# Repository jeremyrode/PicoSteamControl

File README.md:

# PicoSteamControl
This project implements a new Raspberry Pi Pico based control for a [Leisure Steam One Touch LS series steam generator](https://leisure-steam.com/product-category/steam-generators/1-touch-steam-unit/).

The factory control PCB was misbehaving, and I have wanted to implement an automatic self-flush to clean the tank, so I thought it would be a good challenge to replace it with a Raspberry Pi Pico.

This is my first MicroPython project.  I was originally implementing this system in C, but when I started down the path to connect a Pico W to WiFi, I decided to try out MicroPython and I was blown away by the power and rapid development/test cycles.

I mostly think this project might be interesting to people because of a few new ideas that I have not seen documented well in the wild:

# New ideas:

This project served as a testbed for 3 new ideas that I wanted to try:
- Status Logging and Timestamping though WiFi
- Capacitive Touch Sensing via a PIO State Machine
- New Ideal Diode Peak Detector CT Interface

## Status Logging and Timestamping though WiFi

A major reason I was implementing much of my IoT work with boards that run full Linux (usually a Raspberry Pi Zero W) is logging and timestamping functionality.  Many of these IoT systems are very difficult to debug without a persistent log that is timestamped.  Both storing and retrieving persistent logs (to some sort of nonvolatile memory) and getting real time (UTC) on a microcontroller are difficult.

Here, this is solved by sending my log messages out to Raspberry Pi with NTP running via the network and urequests libraries:

```python
def logWifi(logmessage):
    print('Log: ' + logmessage)
    res = requests.post(secrets.url, data = logmessage)
```

Remarkably simple and effective, this server could easily serve many Pico W boards. See main.py for the full code with WiFi reconnection, and error handling.  [The secrets.url uses a config file to not check in WiFi passwords or local IPs to a public Git.]( https://www.coderdojotc.org/micropython/wireless/02-connecting-to-wifi/ "MicroPython WiFi Info")

The logWifi() function in main.py takes the log request and sends it to a http server (SteamLogger.js) running in Node.js that timestamps it and writes it to a file.

```node
const server = http.createServer((req, res) => {
  if (req.method === 'POST') {
    let data = '';
    req.on('data', chunk => {
      data += chunk.toString();
    });
    req.on('end', () => {
      let curDate = new Date();
      let dateStr = curDate.toString();
      message = dateStr.slice(0,dateStr.length-33) + ' ' + data; //Prepend Time to message
      console.log(message);
      logfile.write(message + '\n')
      res.end('OK');
    });
  }
});
```
Note that this code was upgraded into batch mode via Gemini.

## Capacitive Touch Sensing via PIO State Machine

After discovering that the control button on the LS1 one touch is a capacitive membrane switch, I investigated specific ICs that detect capacitive touch sensing, but this is a perfect task for a PIO state machine. This PIO-based detection ended up very reliable and has very good dynamic range: Around 250K cycles for the untouched state, and with a strong push increasing this to 6-8M cycles.  A logging function serves to quantify the reliability. 

Here is a very unoptimized PIO state machine that charges a capacitive touch sensor via an output pin and a resistor, then cycle counts the time to discharge.
[I’ve broke this out into its own repository]( https://github.com/jeremyrode/RaspPiPicoTouchSensor "RaspPiPicoTouchSensor Repo"), and I might try to optimize it eventually.

```
pull(block)                 # Get charge delay val     
mov(x,osr)                  # Load charge delay val    
wrap_target()               # Only do the above once   
mov(y, invert(null))        # Set Y to Large (All Ones)
set(pins, 1)                # Start Charging           
label("innerloop")                                     
jmp(pin, "loopescape")      # If Pin is High, Escape   
jmp(y_dec, "innerloop")     # Loop and decrement Y     
label("loopescape")                                    
mov(isr,y)                  # Move Y to CPU SR         
set(pins, 0)                # Discharge                
push(noblock)               # Push Y                   
mov(y,x)                    # Load charge delay val    
label("chargeloop")                                    
jmp(y_dec, "chargeloop")     # If !Zero, X-- and loop  
wrap()                                                 
```

### How it Works

This code uses a PIO state machine to repeatedly charge and discharge the touch sensor detecting a change in capacitance via the time-to-charge.  The touch sensor is charged via an output pin connected through 1-megaohm resistor (R1 on schematic) giving a RC time delay that can be measured by an input pin connected directly to the touch sensor.

The PIO state machine starts by getting the discharge time via an initial value written to the PIO state machine, that is moved to scratch register X.  This is necessary, as the PIO SET instruction is limited to 31, which is nowhere near the necessary value* (1,250,000).  The state machine then sets Y to all ones, sets the charge pin to "1", and counts down (via the "innerloop") until the jump pin goes low via RC discharge.  The jump escapes the loop (via jumping to "loopescape").  The Y value is outputted by moving Y to the input shift register (ISR) and pushing to the FIFO.  The push is nonblocking, to keep the detections going, but the FIFO will go stale if it's not read periodically.  To prepare for the next detection the charge pin is set to discharge "0", and then the discharge delay is performed, but preserving the charge delay value stored in scratch register X, to Y, then looping via “chargeloop”.  At this point, we return to wrap_target(), which repeats everything (except loading the charge delay to scratch register X).

The user space code calibrates the baseline charge time with an IIR filter, and if a difference (here 4_000_000 cycles or 32 ms) in the charge time is detected a touch event is registered.  The touch detection is debounced via a time delay gate, as a single human-timescale touch event can trigger multiple PIO detections.

*Yes, I’m aware that large values in scratch registers can be set via the bit-reverse function of the MOV instruction, but these are a bit too large, as the smallest value is a SET of 16 (0b10000), bit reversed is 2^27, which is a delay of 1 second (2^27 / 125 MHz).

```python
baseline = 350_000 # Inital state for baseline IIR Value for touch detection (350_000, connected, 4_000 bare PCB)
touch_threshold = 4_000_000 #Threshold above baseline for a touch (4_000_000, connected, 4_000 bare PCB)
time_between_touches_ms = 1000 #Debounce time for a touch
DATA_IIR_CONST = 1000  # Filtering constant for the IIR filter
sm.put(1_250_000, 0)  #This sets Charging Delay and detection rate in SM clock cycles (10 ms)
while True:
    curval = 4_294_967_295 - sm.get() #State Machine counts down from 2^32
    if time.ticks_diff(time.ticks_ms(), last_touch) > time_between_touches_ms: #Not a multi-touch event
        if curval > baseline + touch_threshold: #We have a touch event
            last_touch = time.ticks_ms()
            print('Touch')
        else: #Only start taking button stats after the touch event has passed
            baseline = curval / DATA_IIR_CONST + baseline * (DATA_IIR_CONST - 1) / DATA_IIR_CONST #Take Baseline Stats
```

Here the python sets the discharge delay via sm.put().  An infinite loop pulls the discharge value and changes it into delay counts by subtracting from 2^32.  Here the detection is debounced via a timestamp and compared to a threshold value above a baseline non-touched value.  This code adapts the baseline capacitance via an infinite first-order impulse response (IIR) filter that adapts to any slow varying baseline capacitance.

## New Ideal Diode Peak Detector CT Interface

Interfacing to Current Transformers (CTs) is a real pain; either one needs to bias the signal in the middle of the ADC range, and sample fast enough to capture the 60 Hz sine wave, extracting the RMS, or a diode envelope detector can be used.  The simple diode envelope detector simplifies the ADC reading, as the output signal is DC, but the diode turn-on voltage makes the transfer function non-linear when the signal from the CT is below the diode turn-on voltage, making the current measurement inaccurate at low current.

Here, I’ve tried to make an ideal diode based peak detector (with gain) out of a non-inverting op amp driving though a diode.  Ideally this should both make the ADC readout much simpler and more accurate, as the output is DC, and the time constant can be set via a capacitor, and make the CT more accurate as the burden resistor can be sized optimally for the CT, with the op-amp gain used to optimally fill the ADC range from the typically lower voltage from a CT in the linear regime.

# Schematic:

The factory control board was replaced with a quad relay board from amazon, wired directly to a RJ45 (J2) breakout board from Spark Fun (Pins 8-3). This relay board replaces the factory control board, and is wired into the 220V fill solenoid, drain valve, and the 50A heater contactor.  The relay board is an active low (open collector) on pins 4-7, VCC on pin 4 and ground on pin 1.  I wired a 1600:1 50A Current Transformer (CT) to pins 1 and 2.

The factory touchpad with LED is wired to J1.  From measuring with a meter, the power LED is on Pins 1 and 2 of the RJ12 connector (J1).  The capacitive touch sensor is on pin 4.  I think the ground shield of the cap sensor is on pin 3.

Note that this is the schematic that I built on a proto board with parts on hand.  A PCB with a proper ground is in the PCB directory.

The CT burden resistor (R5) is set at 30 Ohms, calculated for good CT linearity.  The output voltage from the burdgen resistor goes to an op-amp (U2A). Here U2A with feedback around a diode (D1) forms an ideal diode, with feedback though a voltage divider formed by R4/R3, here with a voltage gain of 3.2X.  A 1uF capacitor (C1) stores the peak voltage from the diode (envelope detector), with a discharge time constant of ~32ms (1uF & 32k Ohms).  This voltage is converted by ADC0 of the Pico.

Testing and simulations show this time constant isn't nearly enough by a couple of orders of magnitude, the proper calculation should be how much voltage sag the sampling capacitor has over the 1/60 Hz cycle and this calculation results in the resistor sum greater than a megaohm for 1 LSB of a 12-bit ADC.  Achieving the time constant with larger values can cause opamp instability and overshoot when the current changes.

The unused is set to an non-inverting amp of gain 1 to ground, [as per recommendation.]( https://www.ti.com/lit/ab/sboa204a/sboa204a.pdf)  Note that the op amp used here needs to be rated for a common-mode voltage at the bottom rail (here ground), but not the top rail, as there is headroom between the 3.3V maximum output and the 5V supply.  The [LM358 is rated for VCM down to V- but only to V+ - 2V.](https://www.ti.com/product/LM358#tech-docs)

# Future Ideas
- Higher touch threshold for on than off
- Low/High via separate contactors for each heating element
- Optimize the PIO touch detection
- Single Pin touch detection

## Single Pin Optimized PIO touch detection

Single pin sans resistor touch detection is very possible.  The Pico has pin pull down functionality (it’s on by default), and the IO directionally can be set dynamically via PINDIRS.  The state machine could be made tighter by both slowing down the clock rate such that the delay can be implemented by the SET instruction, and the SIDESET functionality can save a few instructions.

# Errata Discovered for time.ticks_diff()

time.ticks_diff() doesn't seem to like intervals over a few days, the code was hanging.  I have changed the code to use a boolean to keep toggle the state, rather than rely on elapsed time, which seems to not work after a few days.

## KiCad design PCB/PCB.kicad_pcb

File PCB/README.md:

# PicoSteamControl Schematic

No PCB yet, just the schematic I build on a protoboard

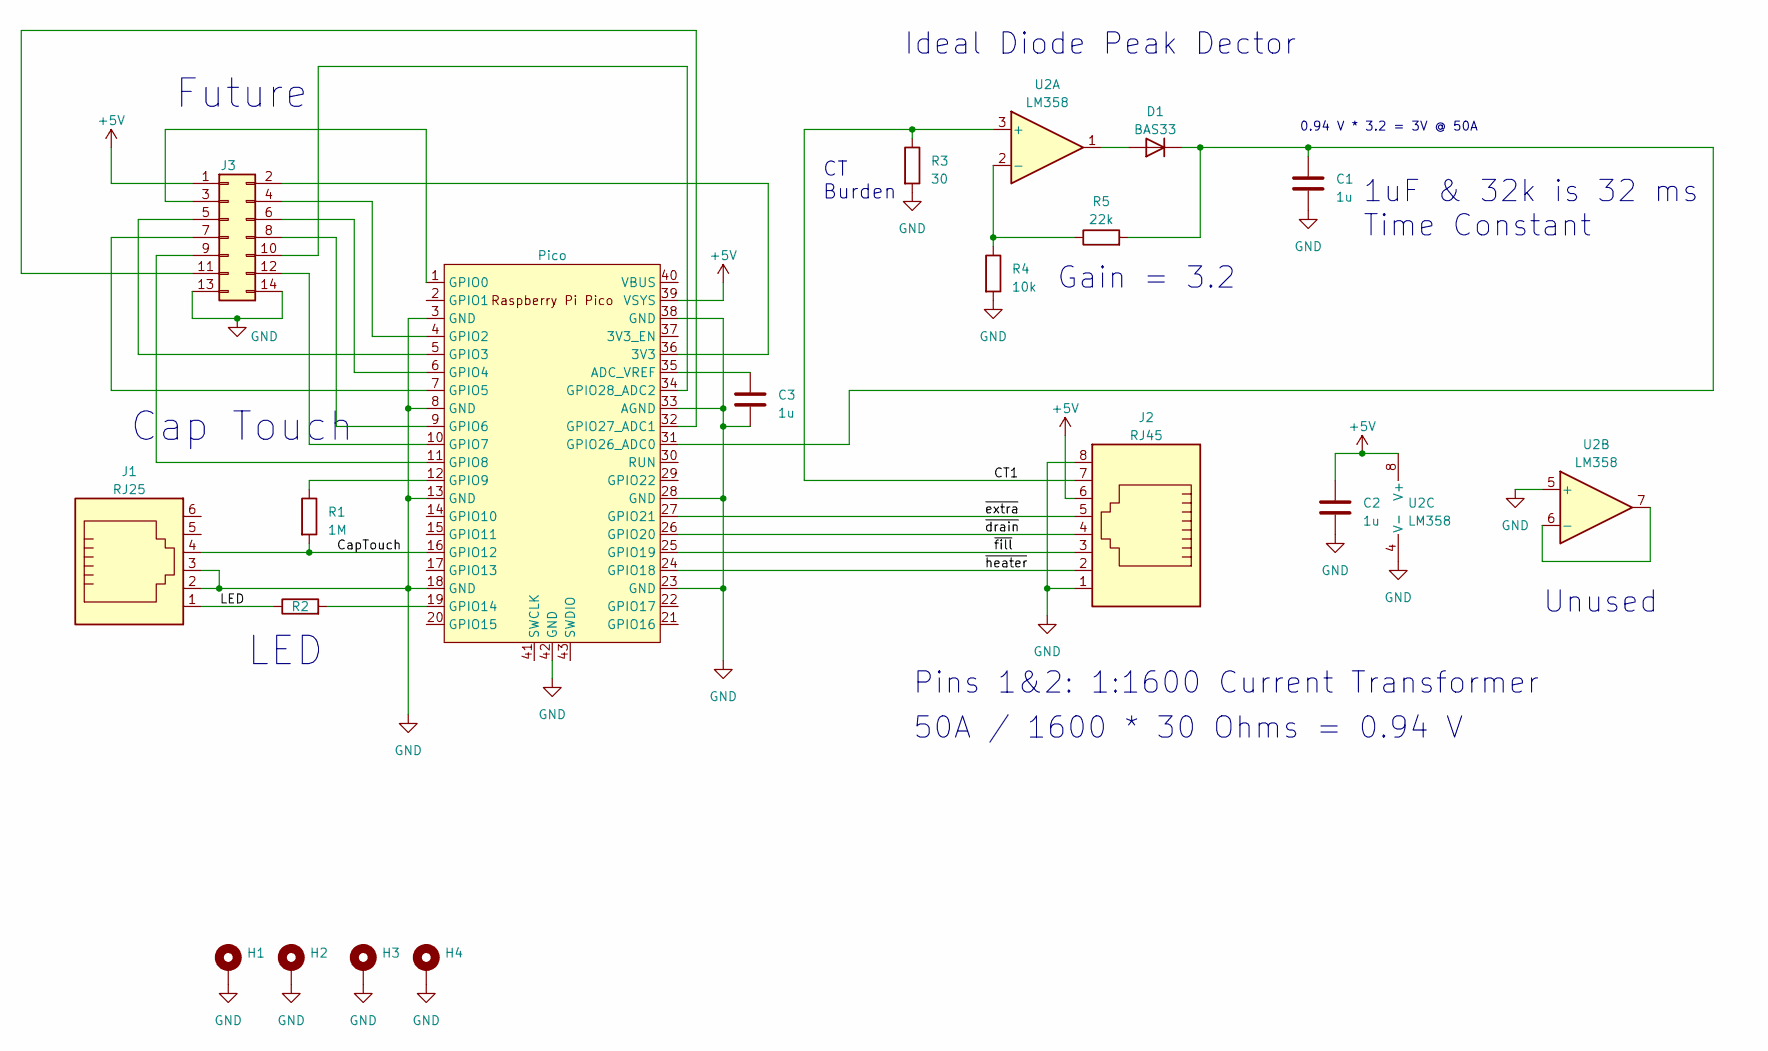
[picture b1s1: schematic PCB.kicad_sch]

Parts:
C1, C2, C3: 1u; C_0805_2012Metric_Pad1.18x1.45mm_HandSolder
D1: BAS33; D_DO-35_SOD27_P7.62mm_Horizontal
H1, H2, H3, H4: MountingHole_Pad; MountingHole_2.7mm_M2.5_Pad
J1: RJ25; RJ25_Wayconn_MJEA-660X1_Horizontal
J2: RJ45; RJ45_Amphenol_54602-x08_Horizontal
J3: Conn_2Rows-07Pins; PinHeader_2x07_P2.54mm_Vertical
R1: 1M; R_0805_2012Metric_Pad1.20x1.40mm_HandSolder
R2: 100; R_0805_2012Metric_Pad1.20x1.40mm_HandSolder
R3: 30; R_0805_2012Metric_Pad1.20x1.40mm_HandSolder
R4: 10k; R_0805_2012Metric_Pad1.20x1.40mm_HandSolder
R5: 22k; R_0805_2012Metric_Pad1.20x1.40mm_HandSolder
U1: Pico; RPi_Pico_SMD
U2: LM358; DIP-8_W10.16mm

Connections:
+5V: C2.1, J2.6, J3.1, U1.39 (VSYS), U2.8 (V+)
/CT1: J2.7, R3.1, U2.3 (+)
/CapTouch: J1.4, R1.2, U1.16 (GPIO12)
/LED: J1.1, R2.1
/~drain: J2.4, U1.26 (GPIO20)
/~extra: J2.5, U1.27 (GPIO21)
/~fill: J2.3, U1.25 (GPIO19)
/~heater: J2.2, U1.24 (GPIO18)
GND: C1.2, C2.2, C3.2, H1.1, H2.1, H3.1, H4.1, J1.2, J1.3, J2.1, J2.8, J3.13, J3.14, R3.2, R4.2, U1.3 (GND), U1.8 (GND), U1.13 (GND), U1.18 (GND), U1.23 (GND), U1.28 (GND), U1.33 (AGND), U1.38 (GND), U1.42 (GND), U2.4 (V-), U2.5 (+)
unnamed: D1.2 (A), U2.1
unnamed: C1.1, D1.1 (K), R5.2, U1.31 (GPIO26_ADC0)
unnamed: J3.2, U1.36 (3V3)
unnamed: J3.3, U1.1 (GPIO0)
unnamed: J3.4, U1.4 (GPIO2)
unnamed: J3.5, U1.5 (GPIO3)
unnamed: J3.6, U1.6 (GPIO4)
unnamed: J3.7, U1.7 (GPIO5)
unnamed: J3.8, U1.9 (GPIO6)
unnamed: J3.9, U1.11 (GPIO8)
unnamed: J3.10, U1.34 (GPIO28_ADC2)
unnamed: J3.11, U1.32 (GPIO27_ADC1)
unnamed: J3.12, U1.10 (GPIO7)
unnamed: C3.1, U1.35 (ADC_VREF)
unnamed: R1.1, U1.12 (GPIO9)
unnamed: R2.2, U1.19 (GPIO14)
unnamed: R4.1, R5.1, U2.2 (-)
unnamed: U2.6 (-), U2.7

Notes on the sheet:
Unused
1uF & 32k is 32 ms Time Constant
Ideal Diode Peak Dector
LED
Future
CT Burden
50A / 1600 * 30 Ohms = 0.94 V
Gain = 3.2
Cap Touch
0.94 V * 3.2 = 3V @ 50A
Pins 1&2: 1:1600 Current Transformer

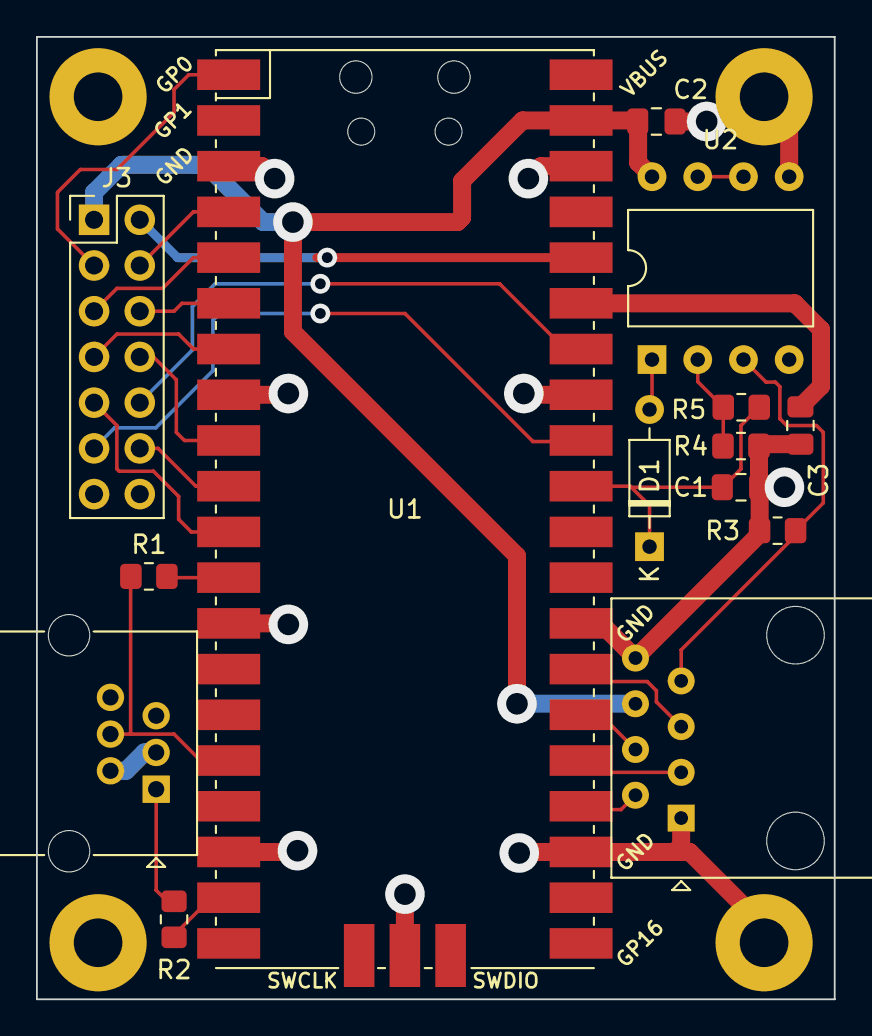
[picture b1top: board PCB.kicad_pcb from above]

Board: 4 copper layers, 44.3 x 53.5 mm, 18 parts (0 on the bottom side), 27 nets.

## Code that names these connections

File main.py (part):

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## Pin Setup / LED
shower_led = machine.Pin(14, mode=machine.Pin.OUT, pull=None, value=0)
wled = machine.Pin("LED", machine.Pin.OUT) #Pico W LED
heater = machine.Pin(18, mode=machine.Pin.OPEN_DRAIN, pull=None, value=1)
fill = machine.Pin(19, mode=machine.Pin.OPEN_DRAIN, pull=None, value=1)
drain = machine.Pin(20, mode=machine.Pin.OPEN_DRAIN, pull=None, value=1)
extra =  machine.Pin(21, mode=machine.Pin.OPEN_DRAIN, pull=None, value=1)
# Turn off internal pull up on jmp pin
sense = machine.Pin(12, mode=machine.Pin.IN, pull=None)
adc = machine.ADC(machine.Pin(26))     # create ADC object on ADC pin
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
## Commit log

2024-10-22 Migration from testing
2024-10-23 state changes
2024-10-26 Testing Current Sensor, testing mode, add schematic
2024-10-26 remove testing junk
2024-10-27 Full functionality, finish readme
2024-10-27 Schematic and readme cleanup
2024-10-27 more readme cleanup
2024-10-30 pcb updates
2024-11-08 gpio on PCB
2024-11-09 found schematic errors
2024-11-09 more schematic changes
2024-11-28 final README tweaks
2024-12-23 trying to fix button press not detected after a few days of idle
2025-03-12 disabled wifi logging due to urequests crashing
2025-08-27 Update README.md
    testing CT interface
2026-03-14 Gemini Extensive Bug Fixes
2026-03-14 stuff found on pi4
2026-03-16 Testing and works
